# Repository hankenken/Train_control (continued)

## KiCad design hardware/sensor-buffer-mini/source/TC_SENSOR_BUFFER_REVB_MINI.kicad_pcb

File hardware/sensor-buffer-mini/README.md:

> **採用対象外（旧アナログ方式）**：ユーザーがToFセンサを指定したため、このバッファ基板案は保管用です。製作・発注には使用しません。

# センサバッファ小型版 Rev B — 45×32mm

**配線前の配置草案です。発注用データではありません。**
旧100×100mm版を保存し、別リビジョンとして小型化しました。面積1,440mm²、旧比85.6%削減。
MCP6004T-I/SL×2、100Ω×8、1nF×8、100nF×2、10µF×1の実装21点と各ネット接続を維持しています。

## 寸法の考え方

- SOIC14を2個と、手直ししやすい0805/1206を維持。JLCPCB実装部品の再選定を最小限にします。
- センサ8組の3線直付け位置を上下4組ずつに分け、配線の引き出しを確保。
- 従来の8組のGND/OUTと別電源パッドを、共通GND・3.3V・8信号の10線へ集約。
- 直付け穴径0.8mm、パッド1.6mm、ピッチ2.0mm、パッド間隔0.4mm。AWG26程度の信号線を目安とし、より線のはんだ上がり後の外径を現物で確認。
- 取付はM2用2.2mm穴4個。中心は(2.8,2.8)、(42.2,2.8)、(2.8,29.2)、(42.2,29.2)mm。
- 現段階では実用的な配置目標寸法であり、理論上の最小寸法を証明したものではありません。最終配線・GND面・信号評価で寸法の微調整が必要になる場合があります。

## 配線が旧Rev Aから変わります

J1とJ11〜J17の個別出力グループは廃止。出力・電源はJ10の2列×5段の直付けパッドへ統合します。
1番は角パッド。上から1/2、3/4、5/6、7/8、9/10という並びです。コネクタは実装しません。

| J10番号 | 信号 | 既存制御基板への接続 |
|---:|---|---|
| 1 | 3.3V | ADCと共通のセンサ用3.3V（JP1後等。総電流確認後） |
| 2 | GND | 共通GND |
| 3 | ADC0 | TC IO J2-3 |
| 4 | ADC1 | TC IO J3-3 |
| 5 | ADC2 | TC IO J4-3 |
| 6 | ADC3 | TC IO J5-3 |
| 7 | ADC4 | TC IO J6-3 |
| 8 | ADC5 | TC IO J7-3 |
| 9 | ADC6 | TC IO J8-3 |
| 10 | ADC7 | TC IO J9-3 |

J2〜J9は各センサ入力で、1=GND、2=3.3V、3=OUT。S0〜S7の印刷はセンサ番号です。
Pololuモジュールのピン配列と番号は同一ではありません。GND/VCC/OUTの信号名で対応させます。
この基板は3.3V専用です。12V・5Vや独立した別電源を接続しません。
10線集約でGNDは共通1本になります。電線の引張り止めを別途設け、コイル電流が流れるGND配線と共用しないでください。

## 確認結果

- 電気ルールERC：0件。
- 配置DRC：0件。既定の最小クリアランス0.2mmで配置を確認。
- 21実装部品の値・フットプリント・端子ネットは旧Rev Aと一致。
- 回路図と基板の100端子割当が一致。
- 銅配線0本、未接続74件。配線・GND面・ADCの信号品質評価は未完了。

既存100mm制御基板や、JLCPCB画面での回転補正には変更を加えていません。
LCSCコード・吸着中心・JLCPCB実装モデルの向きは未確定です。製造用ガーバーは出力していません。

## 再生成

`/usr/bin/python3 build_design.py`は配置案を生成します。将来の配線を上書きするので、配線後は不用意に再実行しません。
メーカー資料は旧Rev Aの`../sensor-buffer/datasheets/Microchip_MCP6004_DS20001733L.pdf`を参照。
`check_draft.py`はKiCadエクスポート済みのERC/DRC/ネットリストと実基板を照合します。

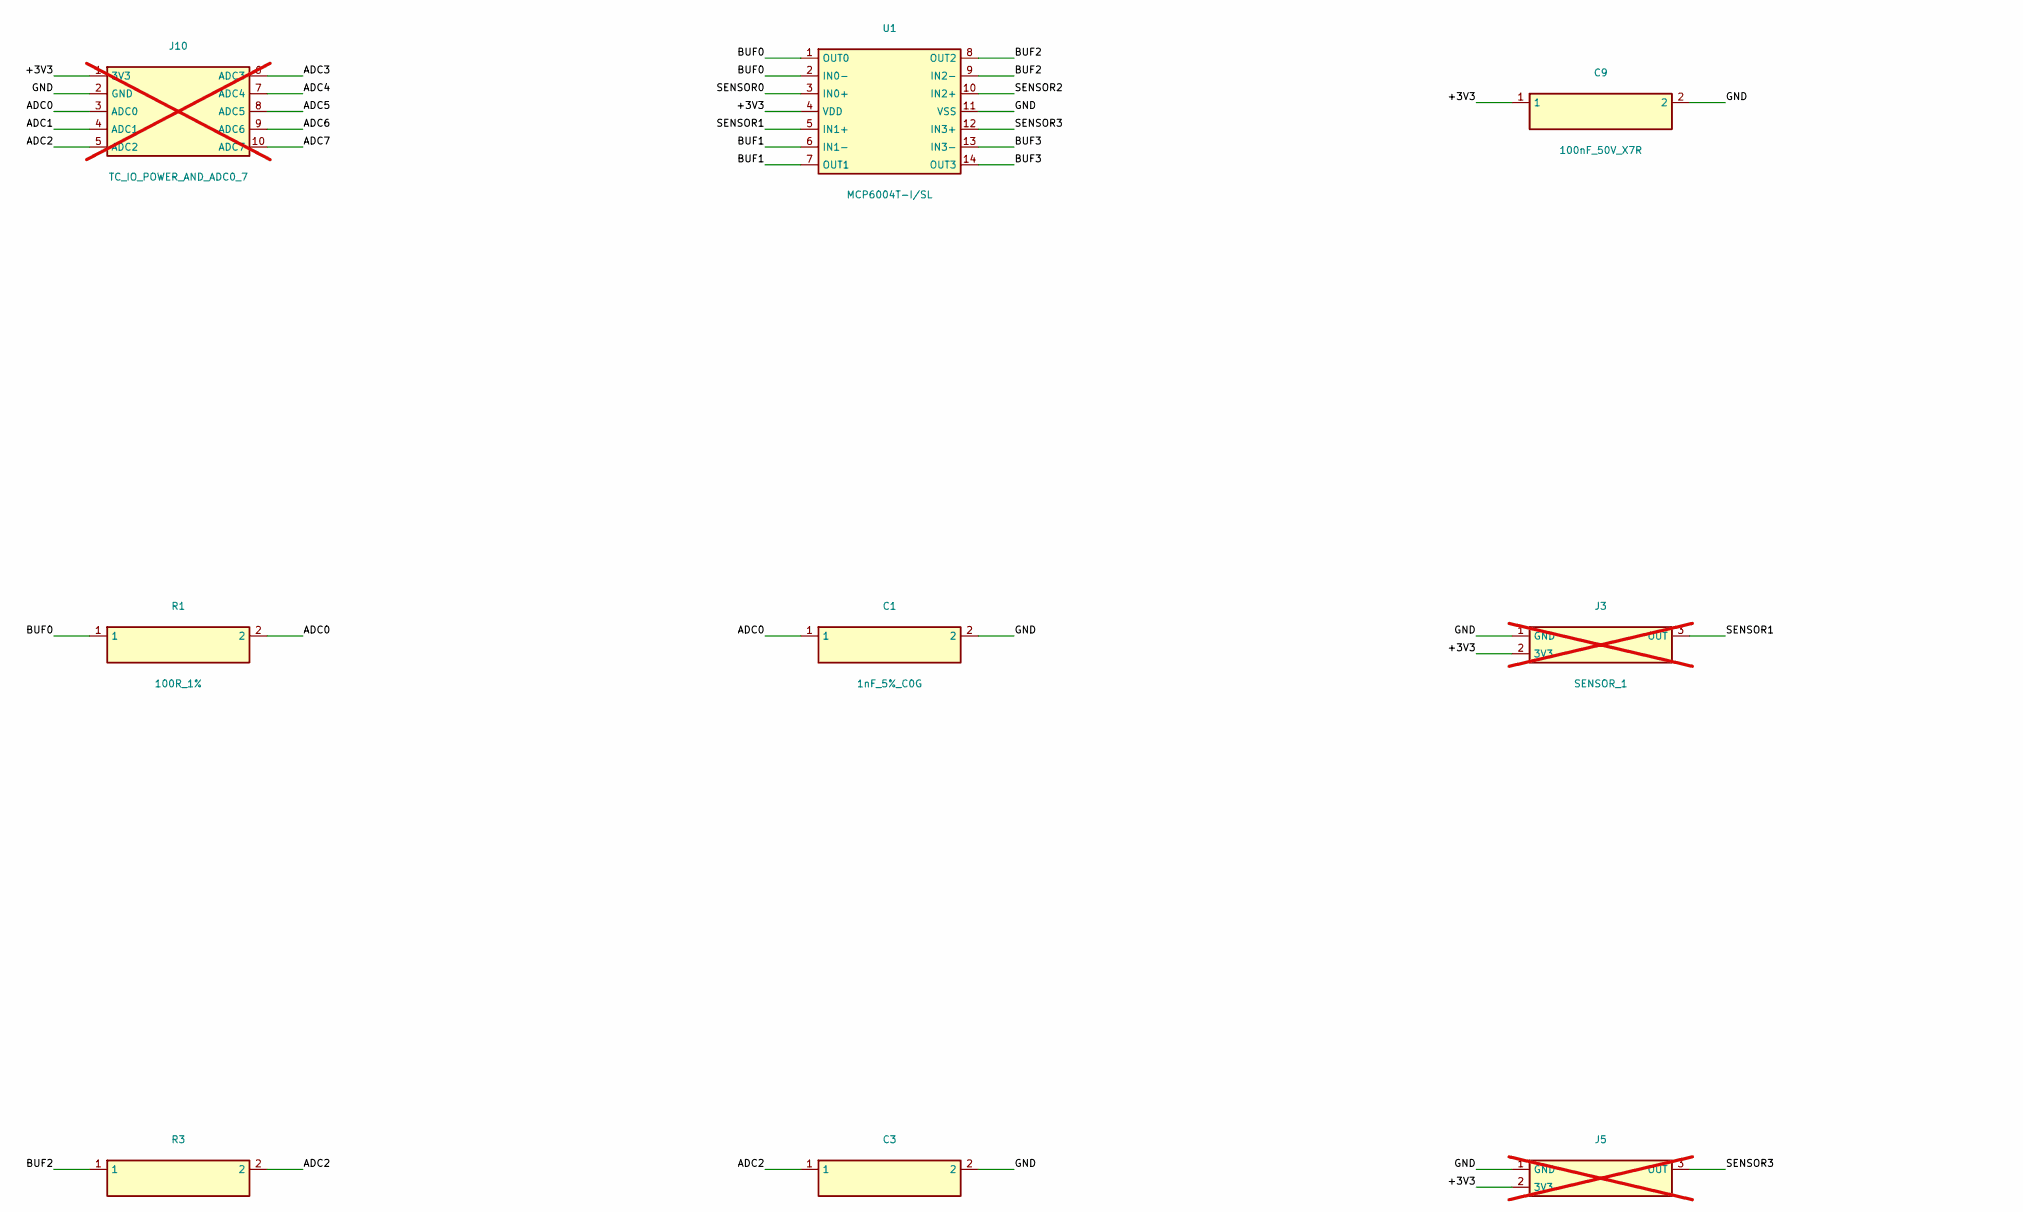
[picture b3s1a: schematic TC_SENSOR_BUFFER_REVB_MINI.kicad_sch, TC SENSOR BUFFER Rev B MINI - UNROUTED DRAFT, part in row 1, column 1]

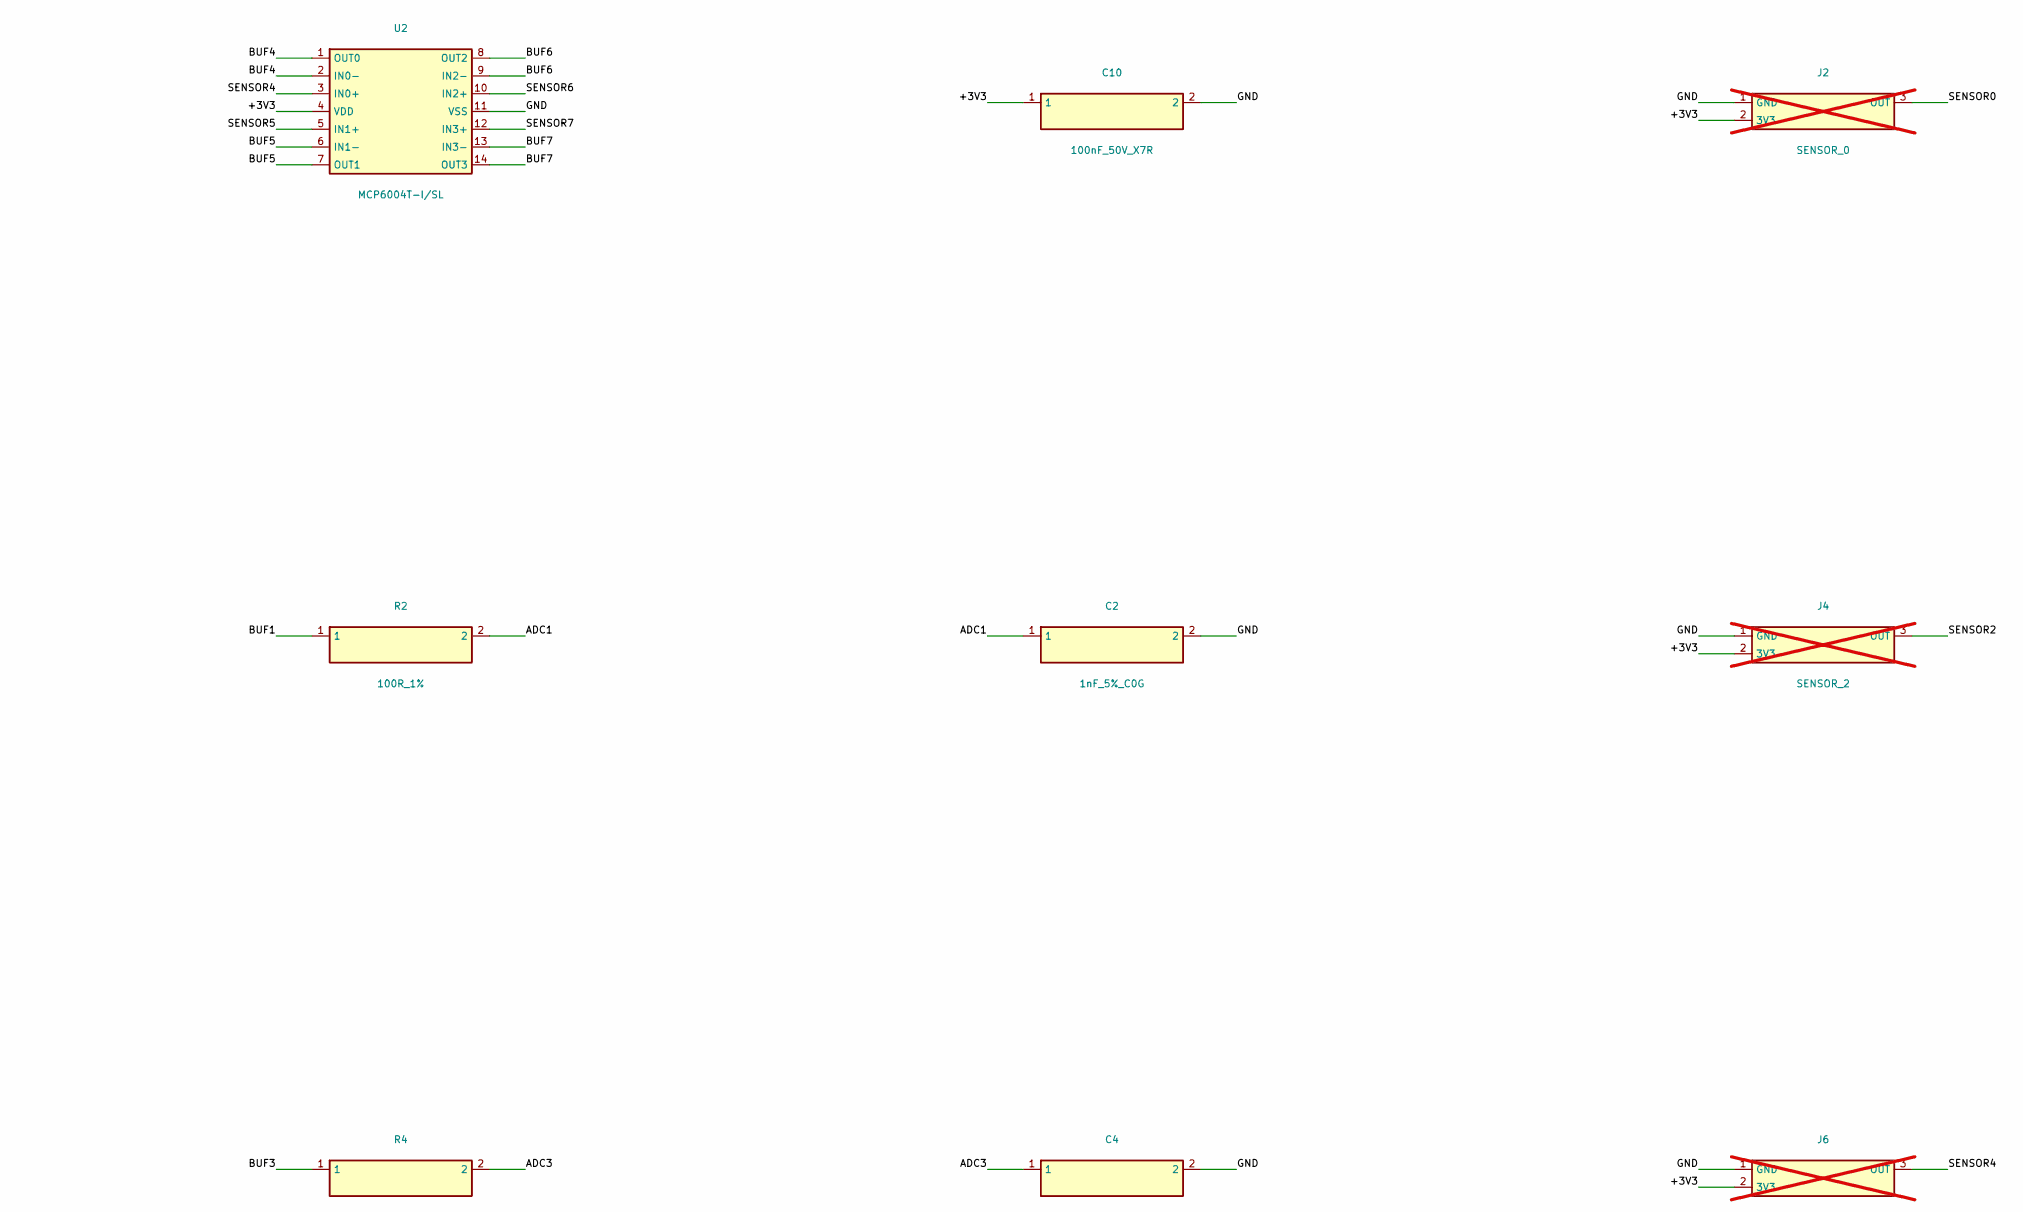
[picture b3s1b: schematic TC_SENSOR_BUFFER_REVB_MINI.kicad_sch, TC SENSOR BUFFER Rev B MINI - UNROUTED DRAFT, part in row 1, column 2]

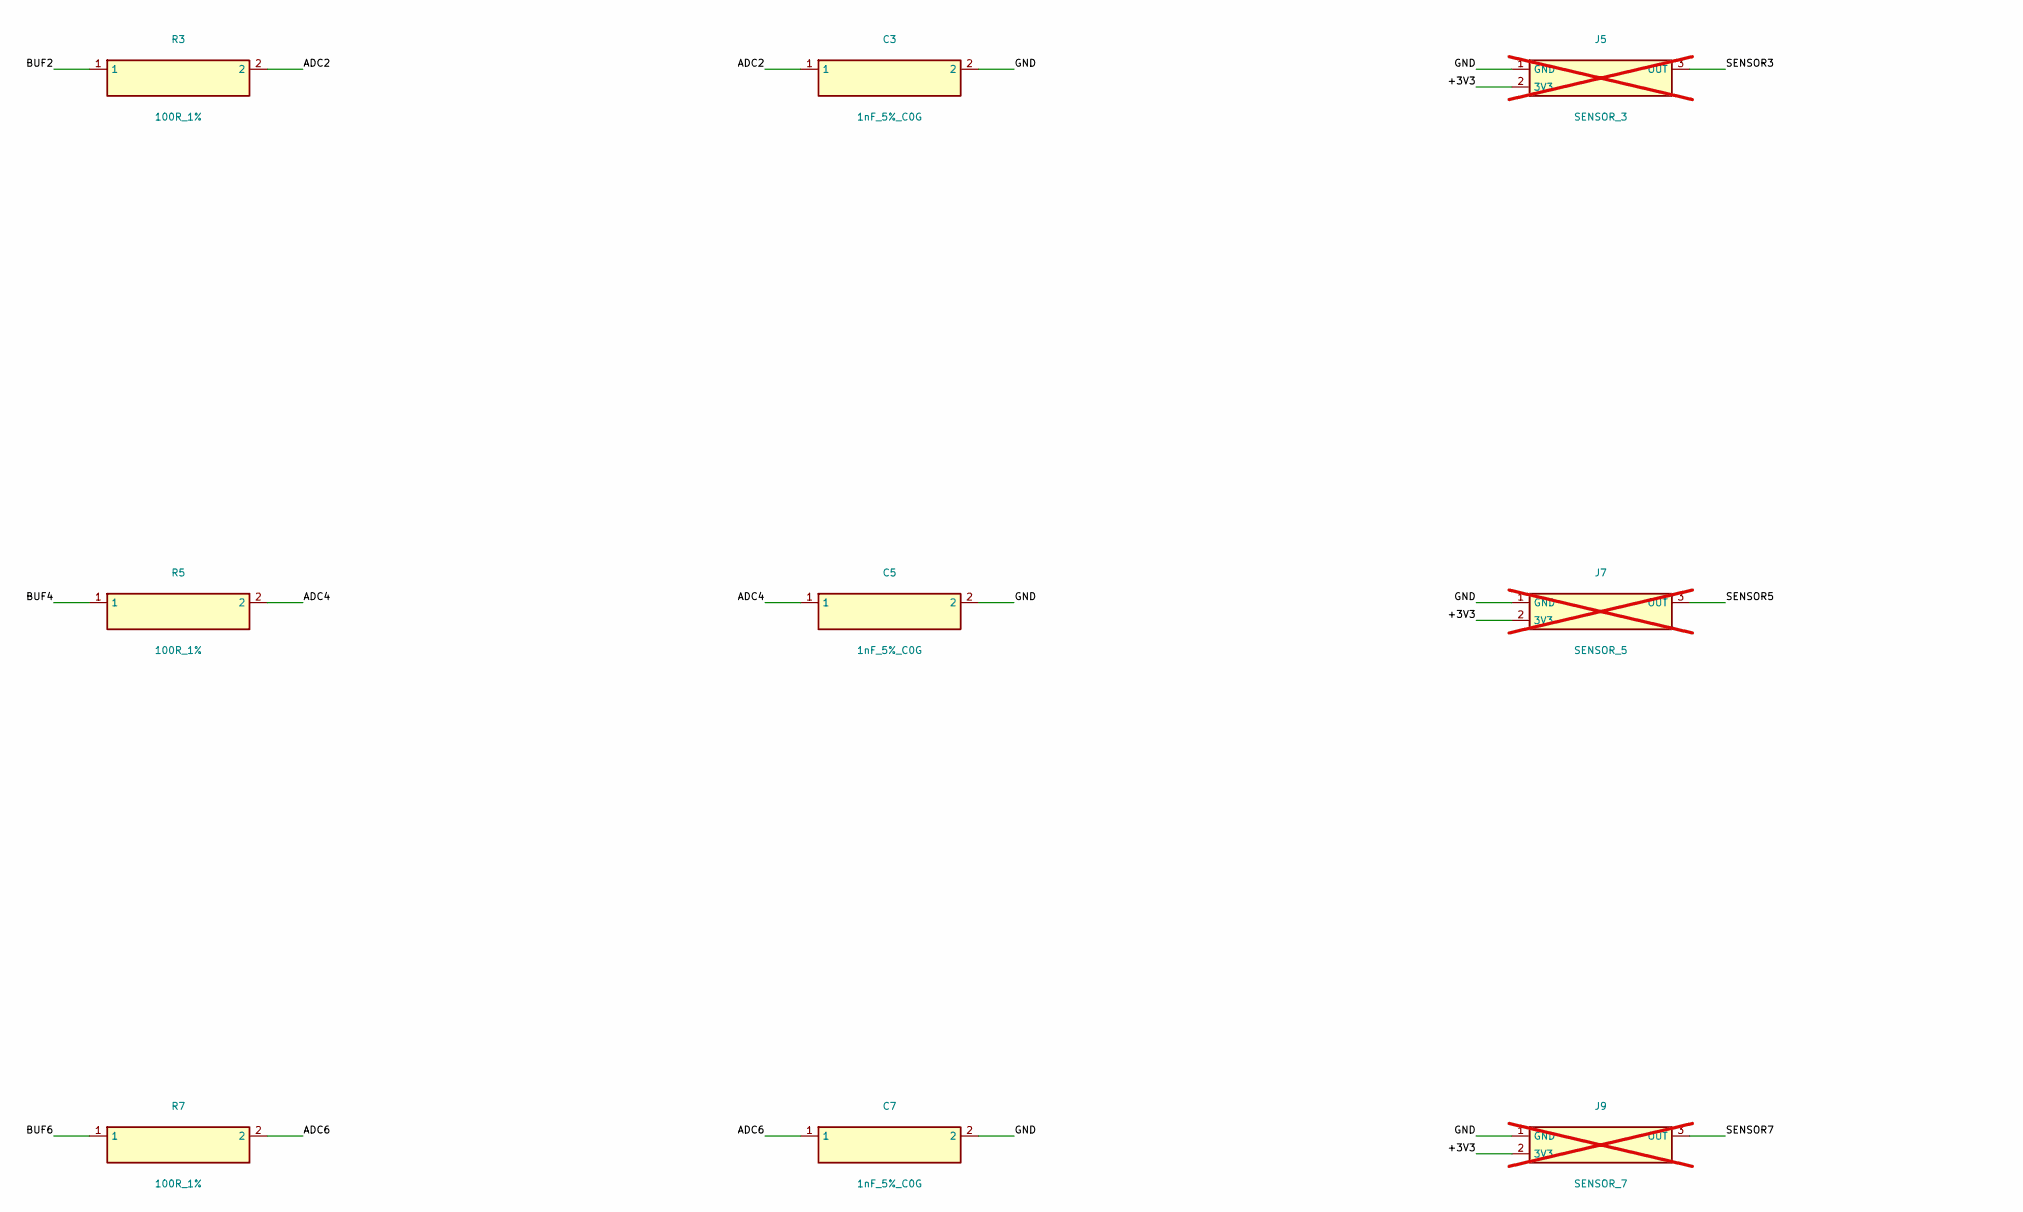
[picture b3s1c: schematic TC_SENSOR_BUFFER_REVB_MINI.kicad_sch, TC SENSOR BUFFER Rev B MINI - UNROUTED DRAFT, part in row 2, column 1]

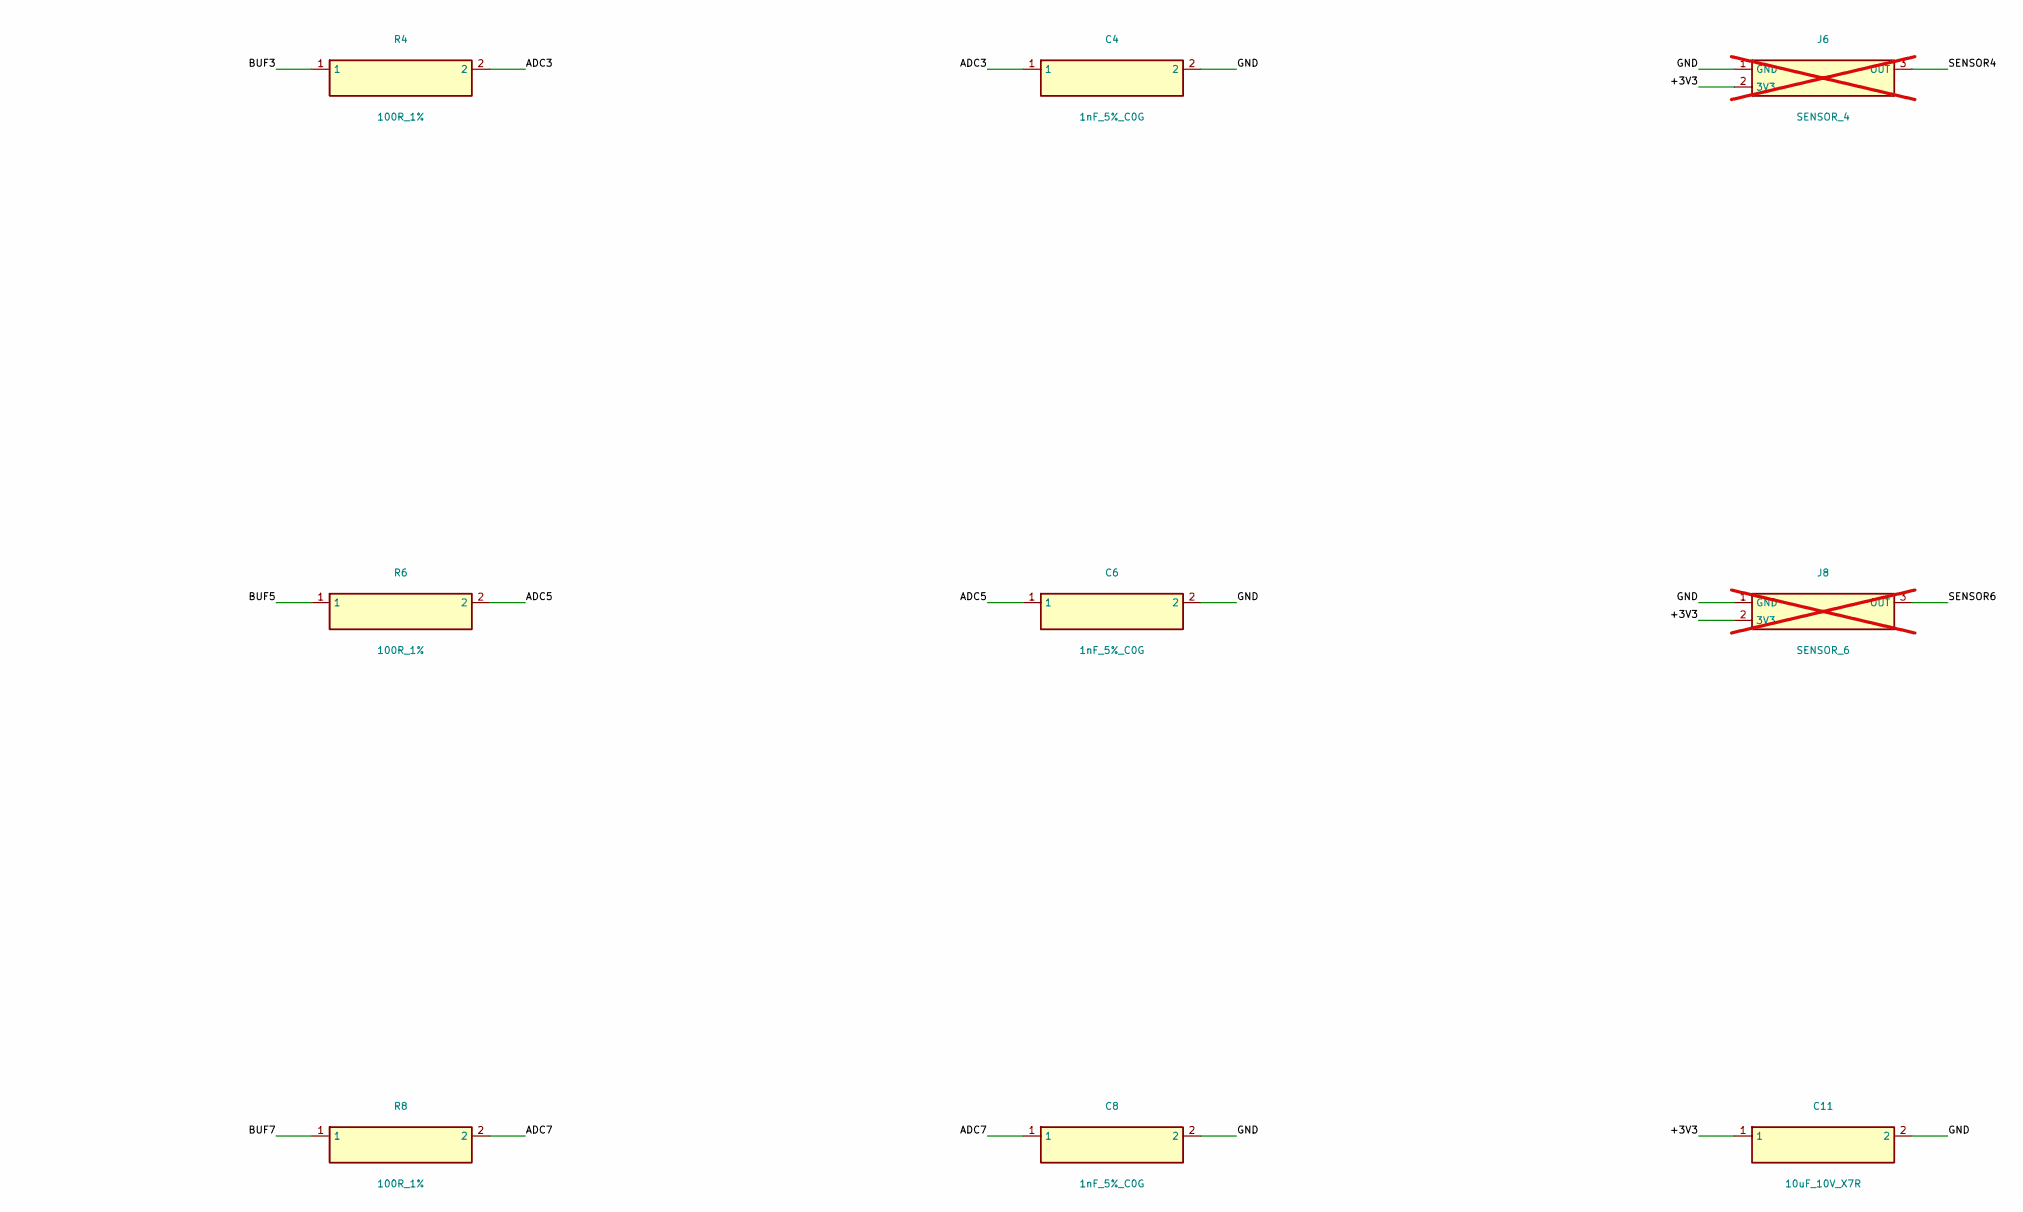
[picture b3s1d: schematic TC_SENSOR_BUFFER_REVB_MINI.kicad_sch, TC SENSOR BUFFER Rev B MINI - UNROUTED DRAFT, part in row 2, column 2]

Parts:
C1, C2, C3, C4, C5, C6, C7, C8: 1nF_5%_C0G; C_0805_2012Metric
C9, C10: 100nF_50V_X7R; C_0805_2012Metric
C11: 10uF_10V_X7R; C_1206_3216Metric
J2: SENSOR_0; Sensor3_P2mm; not fitted
J3: SENSOR_1; Sensor3_P2mm; not fitted
J4: SENSOR_2; Sensor3_P2mm; not fitted
J5: SENSOR_3; Sensor3_P2mm; not fitted
J6: SENSOR_4; Sensor3_P2mm; not fitted
J7: SENSOR_5; Sensor3_P2mm; not fitted
J8: SENSOR_6; Sensor3_P2mm; not fitted
J9: SENSOR_7; Sensor3_P2mm; not fitted
J10: TC_IO_POWER_AND_ADC0_7; Output10_2x5_P2mm; not fitted
R1, R2, R3, R4, R5, R6, R7, R8: 100R_1%; R_0805_2012Metric
U1, U2: MCP6004T-I/SL; SOIC-14_3.9x8.7mm_P1.27mm

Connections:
+3V3: C9.1, C10.1, C11.1, J2.2 (3V3), J3.2 (3V3), J4.2 (3V3), J5.2 (3V3), J6.2 (3V3), J7.2 (3V3), J8.2 (3V3), J9.2 (3V3), J10.1 (3V3), U1.4 (VDD), U2.4 (VDD)
ADC0: C1.1, J10.3 (ADC0), R1.2
ADC1: C2.1, J10.4 (ADC1), R2.2
ADC2: C3.1, J10.5 (ADC2), R3.2
ADC3: C4.1, J10.6 (ADC3), R4.2
ADC4: C5.1, J10.7 (ADC4), R5.2
ADC5: C6.1, J10.8 (ADC5), R6.2
ADC6: C7.1, J10.9 (ADC6), R7.2
ADC7: C8.1, J10.10 (ADC7), R8.2
BUF0: R1.1, U1.1 (OUT0), U1.2 (IN0-)
BUF1: R2.1, U1.6 (IN1-), U1.7 (OUT1)
BUF2: R3.1, U1.8 (OUT2), U1.9 (IN2-)
BUF3: R4.1, U1.13 (IN3-), U1.14 (OUT3)
BUF4: R5.1, U2.1 (OUT0), U2.2 (IN0-)
BUF5: R6.1, U2.6 (IN1-), U2.7 (OUT1)
BUF6: R7.1, U2.8 (OUT2), U2.9 (IN2-)
BUF7: R8.1, U2.13 (IN3-), U2.14 (OUT3)
GND: C1.2, C2.2, C3.2, C4.2, C5.2, C6.2, C7.2, C8.2, C9.2, C10.2, C11.2, J2.1 (GND), J3.1 (GND), J4.1 (GND), J5.1 (GND), J6.1 (GND), J7.1 (GND), J8.1 (GND), J9.1 (GND), J10.2 (GND), U1.11 (VSS), U2.11 (VSS)
SENSOR0: J2.3 (OUT), U1.3 (IN0+)
SENSOR1: J3.3 (OUT), U1.5 (IN1+)
SENSOR2: J4.3 (OUT), U1.10 (IN2+)
SENSOR3: J5.3 (OUT), U1.12 (IN3+)
SENSOR4: J6.3 (OUT), U2.3 (IN0+)
SENSOR5: J7.3 (OUT), U2.5 (IN1+)
SENSOR6: J8.3 (OUT), U2.10 (IN2+)
SENSOR7: J9.3 (OUT), U2.12 (IN3+)

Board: 2 copper layers, 34 parts (0 on the bottom side), 26 nets, no tracks yet.

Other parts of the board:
H1, H2, H3, H4: MountingHole_2.2mm_M2

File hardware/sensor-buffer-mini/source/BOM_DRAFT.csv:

Reference,MPN_or_value,Footprint,Populate,Notes
J10,TC_IO_POWER_AND_ADC0_7,TC_Wire:Output10_2x5_P2mm,False,"NO connector. Direct-wire harness:1=3V3,2=GND,3..10=ADC0..7. One common ground replaces eight duplicate output grounds. Verify wire capacity and strain relief."
U1,MCP6004T-I/SL,Package_SO:SOIC-14_3.9x8.7mm_P1.27mm,True,Unity-gain buffers retained from Rev A. DS20001733L pin roles reviewed. Layout and ADC settling validation pending.
C9,100nF_50V_X7R,Capacitor_SMD:C_0805_2012Metric,True,Bypass. Final traces must minimize supply loop.
U2,MCP6004T-I/SL,Package_SO:SOIC-14_3.9x8.7mm_P1.27mm,True,Unity-gain buffers retained from Rev A. DS20001733L pin roles reviewed. Layout and ADC settling validation pending.
C10,100nF_50V_X7R,Capacitor_SMD:C_0805_2012Metric,True,Bypass. Final traces must minimize supply loop.
J2,SENSOR_0,TC_Wire:Sensor3_P2mm,False,"Direct wires, .8mm drill /1.6mm pad /2mm pitch. Suggested 26AWG class signal wire; confirm tinned bundle fits. Match Pololu by signal name, not pin number."
R1,100R_1%,Resistor_SMD:R_0805_2012Metric,True,Output isolation retained; final route and cable load test required
C1,1nF_5%_C0G,Capacitor_SMD:C_0805_2012Metric,True,Initial analog filter. Not an overvoltage protector
J3,SENSOR_1,TC_Wire:Sensor3_P2mm,False,"Direct wires, .8mm drill /1.6mm pad /2mm pitch. Suggested 26AWG class signal wire; confirm tinned bundle fits. Match Pololu by signal name, not pin number."
R2,100R_1%,Resistor_SMD:R_0805_2012Metric,True,Output isolation retained; final route and cable load test required
C2,1nF_5%_C0G,Capacitor_SMD:C_0805_2012Metric,True,Initial analog filter. Not an overvoltage protector
J4,SENSOR_2,TC_Wire:Sensor3_P2mm,False,"Direct wires, .8mm drill /1.6mm pad /2mm pitch. Suggested 26AWG class signal wire; confirm tinned bundle fits. Match Pololu by signal name, not pin number."
R3,100R_1%,Resistor_SMD:R_0805_2012Metric,True,Output isolation retained; final route and cable load test required
C3,1nF_5%_C0G,Capacitor_SMD:C_0805_2012Metric,True,Initial analog filter. Not an overvoltage protector
J5,SENSOR_3,TC_Wire:Sensor3_P2mm,False,"Direct wires, .8mm drill /1.6mm pad /2mm pitch. Suggested 26AWG class signal wire; confirm tinned bundle fits. Match Pololu by signal name, not pin number."
R4,100R_1%,Resistor_SMD:R_0805_2012Metric,True,Output isolation retained; final route and cable load test required
C4,1nF_5%_C0G,Capacitor_SMD:C_0805_2012Metric,True,Initial analog filter. Not an overvoltage protector
J6,SENSOR_4,TC_Wire:Sensor3_P2mm,False,"Direct wires, .8mm drill /1.6mm pad /2mm pitch. Suggested 26AWG class signal wire; confirm tinned bundle fits. Match Pololu by signal name, not pin number."
R5,100R_1%,Resistor_SMD:R_0805_2012Metric,True,Output isolation retained; final route and cable load test required
C5,1nF_5%_C0G,Capacitor_SMD:C_0805_2012Metric,True,Initial analog filter. Not an overvoltage protector
J7,SENSOR_5,TC_Wire:Sensor3_P2mm,False,"Direct wires, .8mm drill /1.6mm pad /2mm pitch. Suggested 26AWG class signal wire; confirm tinned bundle fits. Match Pololu by signal name, not pin number."
R6,100R_1%,Resistor_SMD:R_0805_2012Metric,True,Output isolation retained; final route and cable load test required
C6,1nF_5%_C0G,Capacitor_SMD:C_0805_2012Metric,True,Initial analog filter. Not an overvoltage protector
J8,SENSOR_6,TC_Wire:Sensor3_P2mm,False,"Direct wires, .8mm drill /1.6mm pad /2mm pitch. Suggested 26AWG class signal wire; confirm tinned bundle fits. Match Pololu by signal name, not pin number."
R7,100R_1%,Resistor_SMD:R_0805_2012Metric,True,Output isolation retained; final route and cable load test required
C7,1nF_5%_C0G,Capacitor_SMD:C_0805_2012Metric,True,Initial analog filter. Not an overvoltage protector
J9,SENSOR_7,TC_Wire:Sensor3_P2mm,False,"Direct wires, .8mm drill /1.6mm pad /2mm pitch. Suggested 26AWG class signal wire; confirm tinned bundle fits. Match Pololu by signal name, not pin number."
R8,100R_1%,Resistor_SMD:R_0805_2012Metric,True,Output isolation retained; final route and cable load test required
C8,1nF_5%_C0G,Capacitor_SMD:C_0805_2012Metric,True,Initial analog filter. Not an overvoltage protector
C11,10uF_10V_X7R,Capacitor_SMD:C_1206_3216Metric,True,

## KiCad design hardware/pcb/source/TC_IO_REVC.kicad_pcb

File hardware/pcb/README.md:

# TC IO Rev C — 100mm角・部品実装依頼の準備

**LCSC調達・JLCPCB実装向けに再設計した候補版です。カタログ確認がネットワーク制限でできておらず、実装注文にはまだ使用できません。**

最新の指定は「IC・抵抗・コンデンサ・VRを実装。コネクタ部品は不要」です。
基板は100×100mm、2層のままです。実装対象は表面実装部品50点、全て表面です。
コネクタは取り付けず、電線直結・測定用の穴を21グループ残します。
旧Rev Bは固定パルス・挿入部品、Rev Cは個別VR・表面実装の設計です。

## 回路と部品の変更

- 8センサ入力、4系統の進路制御、GPIOと配線端子の電気的な割当を維持。
- U1：MCP3008T-I/SL候補、SOIC16。
- U2/U3：CD74HC221M96候補、SOIC16。
- U4〜U6：SN74HC08DR候補、SOIC14。
- U7：MCP100T-300I/TT候補、SOT-23。端子順・検出電圧・解除遅延を提供メーカー資料で確認。実測は未実施。
- 固定抵抗R1〜R26：0805。旧SIP抵抗ネットワークは廃止し、21本の個別プルダウンへ変更。
- C1〜C4：470nF・10%・50VのX7R MLCC、1206。旧フィルム品から変更し、DCバイアス・温度特性の確認が必要。
- C5〜C12：100nF・50VのX7R、0805。C13：10µF・25VのX7R、1206。全て無極性。
- VR1〜VR4：Bourns 3224W-1-104E候補、100kΩの表面実装多回転トリマ。工場実装対象。
- FM1〜FM3：実装位置認識用の基板マーク。購入部品ではない。

「候補」はLCSCで購入・在庫・実装対応を確認できたという意味ではありません。
BOM草案へユーザー提供のLCSCコードと根拠を記録しています。C1〜C4はユーザー指定によりC2167387を採用しました。
現在の部品別状況は[選定状況](pcba/catalog/current-status.md)を参照してください。
DRV8871完成モジュール、センサ、Pi、ポイント、負荷電源は基板外の機器です。

## ファイル

| ファイル | 用途 |
|---|---|
| `TC_IO_REVC_JLCPCB_prototype.zip` | ガーバー・ペースト・穴あけの候補データ。PCBAの確定注文セットではない |
| `TC_IO_REVC_design_package.zip` | 編集元・PDF・BOM/CPL草案・検査結果の資料一式 |
| `source/TC_IO_REVC.kicad_pro` | KiCad 9の編集用プロジェクト |
| `source/TC_IO_REVC.kicad_sch` / `.kicad_pcb` | 回路図 / 基板 |
| `source/TC_Wire.pretty` | コネクタを実装しない直結配線パッドのライブラリ |
| `source/BOM_hand_assembly.csv` | 元部品表。旧ファイル名を維持。Populate=yesだけが実装対象50点 |
| `source/connections.csv` | 全端子・ネット名 |
| `pcba/*BOM_DRAFT_NOT_FOR_ORDER.csv` | 実装部品表の草案。候補型番・数量、未確認のLCSCコードは空欄 |
| `pcba/*CPL_DRAFT_NOT_FOR_ORDER.csv` | 表面実装50点の位置・角度草案。部品モデルとの照合待ち |
| `pcba/excluded-wire-pads.csv` | 実装対象外の配線・測定パッド21グループ |
| `review/TC_IO_REVC_documents.pdf` | 回路図・部品表・接続/VR調整案内をまとめたPDF |
| `review/TC_IO_REVC_schematic.pdf` | 回路図、A1 |
| `review/TC_IO_REVC_BOM.pdf` | 部品表、A4 |
| `review/TC_IO_REVC_assembly.pdf` | 配置図・接続・調整案内 |
| `reports/DRC.json` / `ERC.json` | CAD検査結果 |
| `reports/release-checks.json` | 検査範囲・実装未承認の状態・SHA-256 |

ガーバーだけでは部品実装を注文できません。採用品・LCSC番号・向きを確認したBOM/CPLが必要です。
現在の草案を注文へ投入しないでください。詳しい阻害要因は[PCBA準備状況](pcba/README.md)を参照。

## 基板の仕様案

FR-4、2層、100.000×100.000mm、厚さ1.6mm、外層1oz。面付けなし。
M3用3.2mm穴が4個。外形基準の中心座標は（4,4）、（96,4）、（4,96）、（96,96）mm、中心間隔は92mmです。
実装は表面のみ。コネクタやヘッダは実装せず、配線用のスルーホールへ電線を直付けします。
JLCPCBの実装対応・部品選定を確認してから最終プレビューと見積もりを確認します。

## 電線直結用のパッド

J/JP/TPの番号は接続位置を表す記号です。コネクタ部品を購入・実装する指定ではありません。
1番は角パッドです。基板に取り付ける電線には引張り止めを設け、はんだ部へ力がかからないようにします。

| パッド | 接続 |
|---|---|
| J1 | Piの40端子番号に対応。必要な信号だけ配線。5V端子は本基板で未接続 |
| J2/J3、J4/J5 | 上側外側A/B、上側内側A/B |
| J6/J7、J8/J9 | 下側外側A/B、下側内側A/B |
| J2〜J9 | 1=GND、2=センサ3.3V、3=アナログOUT |
| J10/J11、J12/J13 | 上側外側/内側、下側外側/内側のDRV論理出力 |
| J10〜J13 | 1=GND、2=IN1、3=IN2。12Vやポイントの青白線をつながない |
| J14 | 1=GND、2=3.3V、3=SDA、4=SCL。将来用 |
| JP1 | センサ電源の開放パッド。電流予算を確認するまでは接続しない |
| TP1/TP2 | 1=CLR_N/POWER_GOOD、2=GND |
| TP3〜TP6 | 1=各系統Qパルス、2=GND |

JP1はヘッダを取り付けません。センサ消費電流とPiの3.3V余裕を確認した後に、必要なら短い電線で接続します。
全センサをPiの3.3Vで給電できることはまだ確定していません。
負荷電流は外部DRVの太いGND配線で電源へ戻し、本基板の細いロジック線を使わないでください。

## パルス幅の調整

VR1=上側外側（TP3）、VR2=上側内側（TP4）、VR3=下側外側（TP5）、VR4=下側内側（TP6）。
回路は `3.3V → 固定150kΩ → VR 0〜100kΩ → RCEXT`。CEXT〜RCEXT間は470nFです。
VRの2番摺動端子を3番と接続しています。摺動接点だけが開いた場合は全抵抗側へ戻る構成ですが、全故障に対する保護ではありません。
典型式 `t≈0.7RC` の目安は49.35〜82.25ms。センサ判定やLED切替間隔は変えません。
R1%、C10%、VR10%を仮定した受動部品だけの上側計算は94.64msですが、IC係数、MLCCの温度・DCバイアス特性を含みません。
**100ms以下を保証する回路ではありません。** 負荷未接続で最小・中間・最大位置と使用条件を実測し、必要に応じてR/Cを変更します。
工場実装だけではVRは校正されません。ARM解除中に調整し、単発パルスでまず約50msへ合わせてください。
現在のWebアプリに実機GPIOドライバはなく、基板だけ接続してもポイント制御は始まりません。

## 検査と残作業

CADのDRC/ERC、未接続、回路図と基板のネット一致、VR結線、部品数と実装除外を検証します。
検査結果はreports配下に保存します。CAD検査は部品の購入可否、メーカー仕様、実機正常動作を証明しません。
LCSC番号・在庫・JLCPCB実装対応、採用品の端子/外形、CPLのピン1と回転の照合が未完了です。

接続許可の追加案は環境設定に保存済みです。設定を確認・保存し、環境を公開してからLCSC等への接続を再確認します。
必要ドメインはpcba/README.mdに記録しています。値や認証情報をチャットへ送る必要はありません。

編集はKiCad 9。`build_design.py`は未配線の初期データを上書き生成する開発用です。
配線後は`verify_and_export.py`で検査・製造データ出力、`prepare_pcba_draft.py`でBOM/CPL草案、`export_documents.py`で日本語PDFを作成します。

## タイミング精度の指定変更

ユーザー指定により、C1〜C4をC1206C474K5RACTU（C2167387、470nF±10%）へ変更しました。
厳密な100ms上限精度は要求せず、既存150kΩ＋100kΩVRを維持して実測調整します。

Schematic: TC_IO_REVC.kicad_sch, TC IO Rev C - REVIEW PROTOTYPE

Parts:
C1, C2, C3, C4: 470nF_10%_X7R_50V; C_1206_3216Metric
C5, C6, C7, C8, C9, C10, C11, C12: 100nF_X7R_50V; C_0805_2012Metric
C13: 10uF_X7R_25V; C_1206_3216Metric
J1: WIRE_PADS_NO_COMPONENT; WirePads_2x20_P2.54; not fitted
J2, J3, J4, J5, J6, J7, J8, J9, J10, J11, J12, J13: WIRE_PADS_NO_COMPONENT; WirePads_1x03_P2.50; not fitted
J14: WIRE_PADS_NO_COMPONENT; WirePads_1x04_P2.54; not fitted
JP1: WIRE_PADS_NO_COMPONENT; WirePads_1x02_P2.54; not fitted
R1, R2, R3, R4: 150k_1%; R_0805_2012Metric
R5, R6, R7, R8, R9, R10, R11, R12, R13, R14, R15, R16, R17, R18, R19, R20, R21, R22, R23, R24, R25, R26: 10k_1%; R_0805_2012Metric
TP1, TP2, TP3, TP4, TP5, TP6: WIRE_PADS_NO_COMPONENT; WirePads_1x02_P2.54; not fitted
U1: MCP3008T-I/SL; SOIC-16_3.9x9.9mm_P1.27mm
U2, U3: CD74HC221M96; SOIC-16_3.9x9.9mm_P1.27mm
U4, U5, U6: SN74HC08DR; SOIC-14_3.9x8.7mm_P1.27mm
U7: MCP100T-300I/TT; SOT-23
VR1, VR2, VR3, VR4: 3224W-1-104E; Potentiometer_Bourns_3224W_Vertical

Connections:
+3V3: C5.1, C6.1, C7.1, C8.1, C9.1, C10.1, C11.1, C12.1, C13.1, J1.1, J14.2, JP1.1, R1.1, R2.1, R3.1, R4.1, R5.1, U1.15 (VREF), U1.16 (VDD), U2.16 (VCC), U3.16 (VCC), U4.14 (VCC), U5.14 (VCC), U6.14, U7.2 (VDD)
ADC_CS: J1.24, R5.2, U1.10 (CS)
AN0: J2.3 (OUT), U1.1 (CH0)
AN1: J3.3 (OUT), U1.2 (CH1)
AN2: J4.3 (OUT), U1.3 (CH2)
AN3: J5.3 (OUT), U1.4 (CH3)
AN4: J6.3 (OUT), U1.5 (CH4)
AN5: J7.3 (OUT), U1.6 (CH5)
AN6: J8.3 (OUT), U1.7 (CH6)
AN7: J9.3 (OUT), U1.8 (CH7)
ARM: J1.16, R18.1, U6.1
CLEAR_N: TP1.1, U2.3 (CLR_N), U2.11 (CLR_N), U3.3 (CLR_N), U3.11 (CLR_N), U6.3
GND: C5.2, C6.2, C7.2, C8.2, C9.2, C10.2, C11.2, C12.2, C13.2, J1.6, J1.9, J1.14, J1.20, J1.25, J1.30, J1.34, J1.39, J2.1 (GND), J3.1 (GND), J4.1 (GND), J5.1 (GND), J6.1 (GND), J7.1 (GND), J8.1 (GND), J9.1 (GND), J10.1 (GND), J11.1 (GND), J12.1 (GND), J13.1 (GND), J14.1, R6.2, R7.2, R8.2, R9.2, R10.2, R11.2, R12.2, R13.2, R14.2, R15.2, R16.2, R17.2, R18.2, R19.2, R20.2, R21.2, R22.2, R23.2, R24.2, R25.2, R26.2, TP1.2, TP2.2, TP3.2, TP4.2, TP5.2, TP6.2, U1.9 (DGND), U1.14 (AGND), U2.1 (A_N), U2.8 (GND), U2.9 (A_N), U3.1 (A_N), U3.8 (GND), U3.9 (A_N), U4.7 (GND), U5.7 (GND), U6.4, U6.5, U6.7, U6.9, U6.10, U6.12, U6.13, U7.3 (VSS)
LOW_IN_ADJ: R4.2, VR4.1 (CCW)
LOW_IN_CE: C4.1, U3.6 (CEXT)
LOW_IN_IN1: J13.2 (IN1), R25.1, U5.8 (3Y)
LOW_IN_IN2: J13.3 (IN2), R26.1, U5.11 (4Y)
LOW_IN_N: J1.13, R16.1, U5.12 (4A)
LOW_IN_P: J1.11, R15.1, U5.9 (3A)
LOW_IN_Q: TP6.1, U3.5 (Q), U5.10 (3B), U5.13 (4B)
LOW_IN_RC: C4.2, U3.7 (RCEXT), VR4.2 (WIPER), VR4.3 (CW)
LOW_IN_TRIG: J1.15, R17.1, U3.10 (B)
LOW_OUT_ADJ: R3.2, VR3.1 (CCW)
LOW_OUT_CE: C3.1, U3.14 (CEXT)
LOW_OUT_IN1: J12.2 (IN1), R23.1, U5.3 (1Y)
LOW_OUT_IN2: J12.3 (IN2), R24.1, U5.6 (2Y)
LOW_OUT_N: J1.40, R13.1, U5.4 (2A)
LOW_OUT_P: J1.38, R12.1, U5.1 (1A)
LOW_OUT_Q: TP5.1, U3.13 (Q), U5.2 (1B), U5.5 (2B)
LOW_OUT_RC: C3.2, U3.15 (RCEXT), VR3.2 (WIPER), VR3.3 (CW)
LOW_OUT_TRIG: J1.37, R14.1, U3.2 (B)
MISO: J1.21, U1.12 (DOUT)
MOSI: J1.19, U1.11 (DIN)
POWER_GOOD: TP2.1, U6.2, U7.1 (RESET_N)
SCL: J1.5, J14.4
SCLK: J1.23, U1.13 (CLK)
SDA: J1.3, J14.3
SENSOR_3V3: J2.2 (VCC_3V3), J3.2 (VCC_3V3), J4.2 (VCC_3V3), J5.2 (VCC_3V3), J6.2 (VCC_3V3), J7.2 (VCC_3V3), J8.2 (VCC_3V3), J9.2 (VCC_3V3), JP1.2
UP_IN_ADJ: R2.2, VR2.1 (CCW)
UP_IN_CE: C2.1, U2.6 (CEXT)
UP_IN_IN1: J11.2 (IN1), R21.1, U4.8 (3Y)
UP_IN_IN2: J11.3 (IN2), R22.1, U4.11 (4Y)
UP_IN_N: J1.36, R10.1, U4.12 (4A)
UP_IN_P: J1.33, R9.1, U4.9 (3A)
UP_IN_Q: TP4.1, U2.5 (Q), U4.10 (3B), U4.13 (4B)
UP_IN_RC: C2.2, U2.7 (RCEXT), VR2.2 (WIPER), VR2.3 (CW)
UP_IN_TRIG: J1.35, R11.1, U2.10 (B)
UP_OUT_ADJ: R1.2, VR1.1 (CCW)
UP_OUT_CE: C1.1, U2.14 (CEXT)
UP_OUT_IN1: J10.2 (IN1), R19.1, U4.3 (1Y)
UP_OUT_IN2: J10.3 (IN2), R20.1, U4.6 (2Y)
UP_OUT_N: J1.31, R7.1, U4.4 (2A)
UP_OUT_P: J1.29, R6.1, U4.1 (1A)
UP_OUT_Q: TP3.1, U2.13 (Q), U4.2 (1B), U4.5 (2B)
UP_OUT_RC: C1.2, U2.15 (RCEXT), VR1.2 (WIPER), VR1.3 (CW)
UP_OUT_TRIG: J1.32, R8.1, U2.2 (B)
